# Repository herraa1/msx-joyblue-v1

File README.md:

# Bluetooth controller adapter for MSX (msx-joyblue) v1

Connect Bluetooth controllers to [MSX computers](https://www.msx.org/wiki/)

> [!NOTE]
>
> An adapter based on PCB v1 Build1a has been successfully built and tested using the bluepad32 firmware!
>
> Adapter v1 Build2b has NOT yet been built, although I may build it in the future.
>
> The other builds will NOT be built, and are just left for reference.
>

For an upgraded SMD version, please visit [msx-joyblue-v2](https://github.com/herraa1/msx-joyblue-v2).

## Introduction

The msx-joyblue is an adapter that allows connecting Bluetooth controllers to [MSX general purpose ports](https://www.msx.org/wiki/General_Purpose_port).

The adapter is based on the [unijoysticle2](https://github.com/ricardoquesada/unijoysticle2) and [bluepad32](https://github.com/ricardoquesada/bluepad32) projects, both owned by Ricardo Quesada.

The main features of the msx-joyblue v1 adapter are:
* small size
* made of widely available electronic components
* uses easy to solder through-hole components to lower the skills needed to build the adapter
* emulates up to two MSX joysticks
* attaches to MSX computers using female standard DE9 connectors
* formally requires an external USB power supply as the adapter draws slightly more current than two MSX ports can officially provide
* optionally, can be powered using MSX general purpose ports without an external power supply if your MSX can safely supply enough current
* builtin leds provide information about the operation of the adapter

## [Hardware](hardware/kicad/)

The msx-joyblue v1 adapter uses an ESP32-WROOM-32E based development board (either a [ESP32-DevKitC-32E](https://www.espressif.com/en/products/devkits/esp32-devkitc) board or a [NodeMCU-32 V1.3](docs/NodeMCU32-S_specification_V1.3.pdf) board) to convert the Bluetooth controller actions to the [MSX joystick standard signalling](https://www.msx.org/wiki/Joystick_control).

A printed circuit board (PCB) is used to easily bind all components:
* The ESP32 adapter board is connected using female headers
* PH2.0 connectors are used to connect cable extensions
* A 2.54 pitch I2C header is added for future extensions
* Jumpers are provided to enable different power options
* Only through-hole components are used

Connection to the MSX general purpose ports is implemented using a DE9 joystick extension cables with a female DE9 connector on one side and a loose end on the other side.
The MSX joystick extension cable loose end is wired according to the following pinout mapping.

|  |
|:--|
| MSX joystick connector pinout, from controller plug side |

| MSX side pin | Cable color (may vary) | Signal |
| ------------ | ---------------------- | ------ |
| 5            | Brown                  | +5v    |
| 4            | Orange                 | RIGHT  |
| 3            | Grey                   | LEFT   |
| 2            | Black                  | DOWN   |
| 1            | Red                    | UP     |
| 6            | Green                  | TRIG1  |
| 7            | White                  | TRIG2  |
| 8            | Blue                   | STROBE |
| 9            | Yellow                 | GND    |

### Build1a

[Bill Of Materials (BoM)](https://htmlpreview.github.io/?https://raw.githubusercontent.com/herraa1/msx-joyblue-v1/main/hardware/kicad/msx-joyblue-v1/bom/ibom.html)

The Build1a adapter ignores the MSX general purpose pin8 (OUT) signal. This is not a problem in general, but can cause incompatibilities with specific software, like MSX-HID [^2], which uses pin8 to try to guess which kind of device is connected to a MSX general purpose port. For MSX-HID, holding the Trigger B button, will put the software in FM-Towns compatible mode which will make the adapter functional.

This build uses open collector outputs (via [74LS05 hex inverters with open collector outputs](https://www.ti.com/lit/ds/symlink/sn7405.pdf)) which makes the adapter safer [^3] than the standard MSX joystick schematic depicted in the MSX Technical Data Book, as it avoids a series of undesired conditions that can lead to bus contention/short circuits.

||
|:--|
|msx-joyblue-v1 Build1a without case|

### Build2 (deprecated)

> [!WARNING]
> Build2 will not be finally built! Use at your own risk!
>
> Build2 has been superseded by Build2b.

The Build2 adapter takes into account the MSX general purpose pin8 (OUT) signal:
* When pin8 is HIGH, the adapter puts all stick and triggers signals in high impedance mode irrespective of their status (as if stick and triggers were not hold in the standard MSX joystick schematic), which become HIGH on the MSX side via the MSX PSG related circuitry pull-ups (matching the expected behavior)
* When pin8 is LOW
  * if a stick direction or trigger is hold, the corresponding signal is pulled down to GND causing it to be LOW (matching the expected behavior)
  * if a stick direction or trigger is not hold, the corresponding signal is put in high impedance mode, which becomes HIGH on the MSX side via the MSX PSG related circuitry pull-ups (matching the expected behavior)
  
This build uses discrete logic components to honor the pin8 signaling (a [74LS04 hex inverter](https://www.ti.com/lit/ds/symlink/sn74ls04.pdf) and three [74LS03 quad 2-input positive-nand gates with open collector outputs](https://www.ti.com/lit/ds/symlink/sn74ls03.pdf)) and uses open collector outputs which makes the adapter safer [^3] than the standard MSX joystick schematic depicted in the MSX Technical Data Book, as it avoids a series of undesired conditions that can lead to bus contention/short circuits.

||
|:--|
|msx-joyblue-v1 Build2 render|

### Build2b

> [!WARNING]
> Build2b has NOT yet been tested! Use at your own risk!

The Build2b is similar to Build2 but simplifies the BOM by using less different components.
 
This build uses discrete logic components to honor the pin8 signaling (four [74LS03 quad 2-input positive-nand gates with open collector outputs](https://www.ti.com/lit/ds/symlink/sn74ls03.pdf)) and uses open collector outputs which makes the adapter safer [^3] than the standard MSX joystick schematic depicted in the MSX Technical Data Book, as it avoids a series of undesired conditions that can lead to bus contention/short circuits.

||
|:--|
|msx-joyblue-v1 Build2b render|

### Build3

> [!WARNING]
> Build3 will not be finally built! Use at your own risk!

The Build3 adapter takes into account the MSX general purpose pin8 (OUT) signal, and produces outputs exactly as described for Build2.
  
This build uses GALs, instead of discrete logic components, to honor the pin8 signaling (two [ATF16V8B Electrically-Erasable Programmable Logic Device](https://ww1.microchip.com/downloads/en/devicedoc/atmel-0364-pld-atf16v8b-8bq-8bql-datasheet.pdf)) and uses open collector outputs which makes the adapter safer [^3] than the standard MSX joystick schematic depicted in the MSX Technical Data Book, as it avoids a series of undesired conditions that can lead to bus contention/short circuits.

||
|:--|
|msx-joyblue-v1 Build3 render|

## [Firmware](https://github.com/ricardoquesada/bluepad32/tree/develop)

The msx-joyblue v1 adapter firmware uses Ricardo Quesada [bluepad32](https://github.com/ricardoquesada/bluepad32/tree/main) library to drive Bluetooth controllers.
A [small modification](https://github.com/ricardoquesada/bluepad32/commit/9736bd169bc13ec625d469b8305d2ed2f46d6e69) to the library that enables support for MSX computers was commited to the _develop_ branch. The _main_ branch carries too the modification since February 2024.

See the [bluepad32 documentation](https://github.com/ricardoquesada/bluepad32/tree/main/docs) for [supported Bluetooth controllers](https://github.com/ricardoquesada/bluepad32/blob/main/docs/supported_gamepads.md).

## [Enclosure](enclosure/)

A simple acrylic enclosure is included.

||
|:--|
|msx-joyblue-v1 Build1a inside tested case prototype|

## Powering the msx-joyblue adapter

The msx-joyblue adapter uses about ~107mA when operating, while a single MSX general purpose port is capable of delivering up to 50mA according to the MSX standard [^1].
That means that even using two MSX general purpose ports (50mA + 50mA = 100mA) we are slightly over (107mA) the max current specification for the MSX general purpose ports.

Thus, the safest way to power the msx-joyblue adapter is by powering it via the USB micro connector of the attached ESP32 board using an external 5V USB power supply. The board automatically powers up when using the USB micro connector without enabling any switch.

Nevertheless, even if the MSX especification puts such a low limit on the current that can be drawn from a general purpose port, real MSX hardware usually can safely deliver enough current for the msx-joyblue adapter to work correctly without harming our beloved classic computers.

Taking that into account, the msx-joyblue adapter has been enabled to be optionally powered by the MSX general purpose ports port A and port B.

To enable powering the msx-joyblue adapter from port A and/or port B, the switch J3 _JOY PWR_ must be first turned on by sliding the switch handle to the right.

> [!NOTE]
> A [1N5817 Schottky diode](https://www.onsemi.com/download/data-sheet/pdf/1n5817-d.pdf) D1 is used to avoid leaking current from the msx-joyblue adapter to the MSX in case the msx-joyblue adapter is powered by USB.
> And two Positive Temperature Coeficient (PTC) resettable fuses F3 and F4 of 50mA each protect the MSX general purpose ports port A and port B from excess of current in case something goes horribly wrong on the msx-joyblue adapter side, aligning to the MSX specification.

To power the msx-joyblue adapter using the MSX general purpose ports we must first understand how the PTC protections on the msx-joyblue adapter are implemented.

The selected PTCs are rated for 50mA which is the so called Hold Current (the maximum current that can flow in normal operation). There is also the Trip Current (the minimum current necessary for the PTC to move to high-resistance state) which for the selected PTCs is around 100mA. Those thresholds are dependent on temperature and voltage. And to make things more undeterministic, the behavior of the PTC when current is between those thresholds is undefined (it may trip or not).

In normal operation and for a room temperature of around 25 degrees Celsius, the selected PTCs in practice never trip below 75mA.

So **if our MSX computer can safely provide more than 50mA on each MSX general purpose port** (which is usually the case), we can connect both Port A and port B to the MSX computer and turn on the J3 _JOY PWR_ switch to power the msx-joyblue adapter. Note that we need to connect both ports even if we use just one Bluetooth gamepad, just to meet the power requirements.

From PCB board version 1a, two jumpers JP3 and JP4 can be used to bypass the PTC protections for port A and port B.

> [!WARNING]
> Bypassing the PTC protections may damage your MSX computer.
> Do not bypass the PTC protections unless you known what you are doing.

By closing JP3 (and/or JP4) and **if our MSX computer can safely provide more than 100mA on a single MSX general purpose port**, we can connect Port A (or Port B) to the MSX computer and turn on the J3 _JOY PWR_ switch to power the msx-joyblue adapter using a single joystick port.

In summary, we can use the following options to power the msx-joyblue adapter (from safest to less safe):
* via the ESP32 USB micro conector
  * leave open jumpers J3 and J4
  * turn off the J3 _JOY PWR_ switch
  * connect a 5V USB power supply to the ESP32 USB micro connector
* via two MSX general purpose ports, if your MSX can safely provide slightly more than 50mA on each MSX general purpose port
  * leave open jumpers J3 and J4
  * turn on the J3 _JOY PWR_ switch
  * connect both Port A and Port B to the MSX general purpose ports
* via one MSX general port, if your MSX can safely provide more than 100mA on each MSX general purpose port
  * close jumpers J3 and/or J4
  * turn on the J3 _JOY PWR_ switch
  * connect Port A or Port B to a MSX general purpose port

## Compatibility Tests

| **Model**                | **Adapter PCB v1 Build1a** |
|--------------------------|----------------------------|
| Sony MSX HB-101P         |          OK                |
| Sony MSX HB-501F         |          OK                |
| Toshiba MSX HX-10        |          OK                |
| Philips MSX2 VG-8235     |          OK                |
| Panasonic MSX2+ FS-A1WSX |          OK                |
| Omega MSX2+              |          OK                |
| MSXVR                    |          OK                |

## References

Ricardo Quesada bluepad32 library
* https://github.com/ricardoquesada/bluepad32

Ricardo Quesada Unijoysticle2 project
* https://github.com/ricardoquesada/unijoysticle2

MSX General Purpose port
* https://www.msx.org/wiki/General_Purpose_port

[^1]: https://www.msx.org/wiki/General_Purpose_port
[^2]: https://www.msx.org/wiki/MSX-HID
[^3]: https://www.msx.org/wiki/Joystick/joypad_controller (see "Undesired Conditions")

## Image Sources

* https://www.oshwa.org/open-source-hardware-logo/
* https://en.wikipedia.org/wiki/File:Numbered_DE9_Diagram.svg
* https://commons.wikimedia.org/wiki/File:Bluetooth.svg

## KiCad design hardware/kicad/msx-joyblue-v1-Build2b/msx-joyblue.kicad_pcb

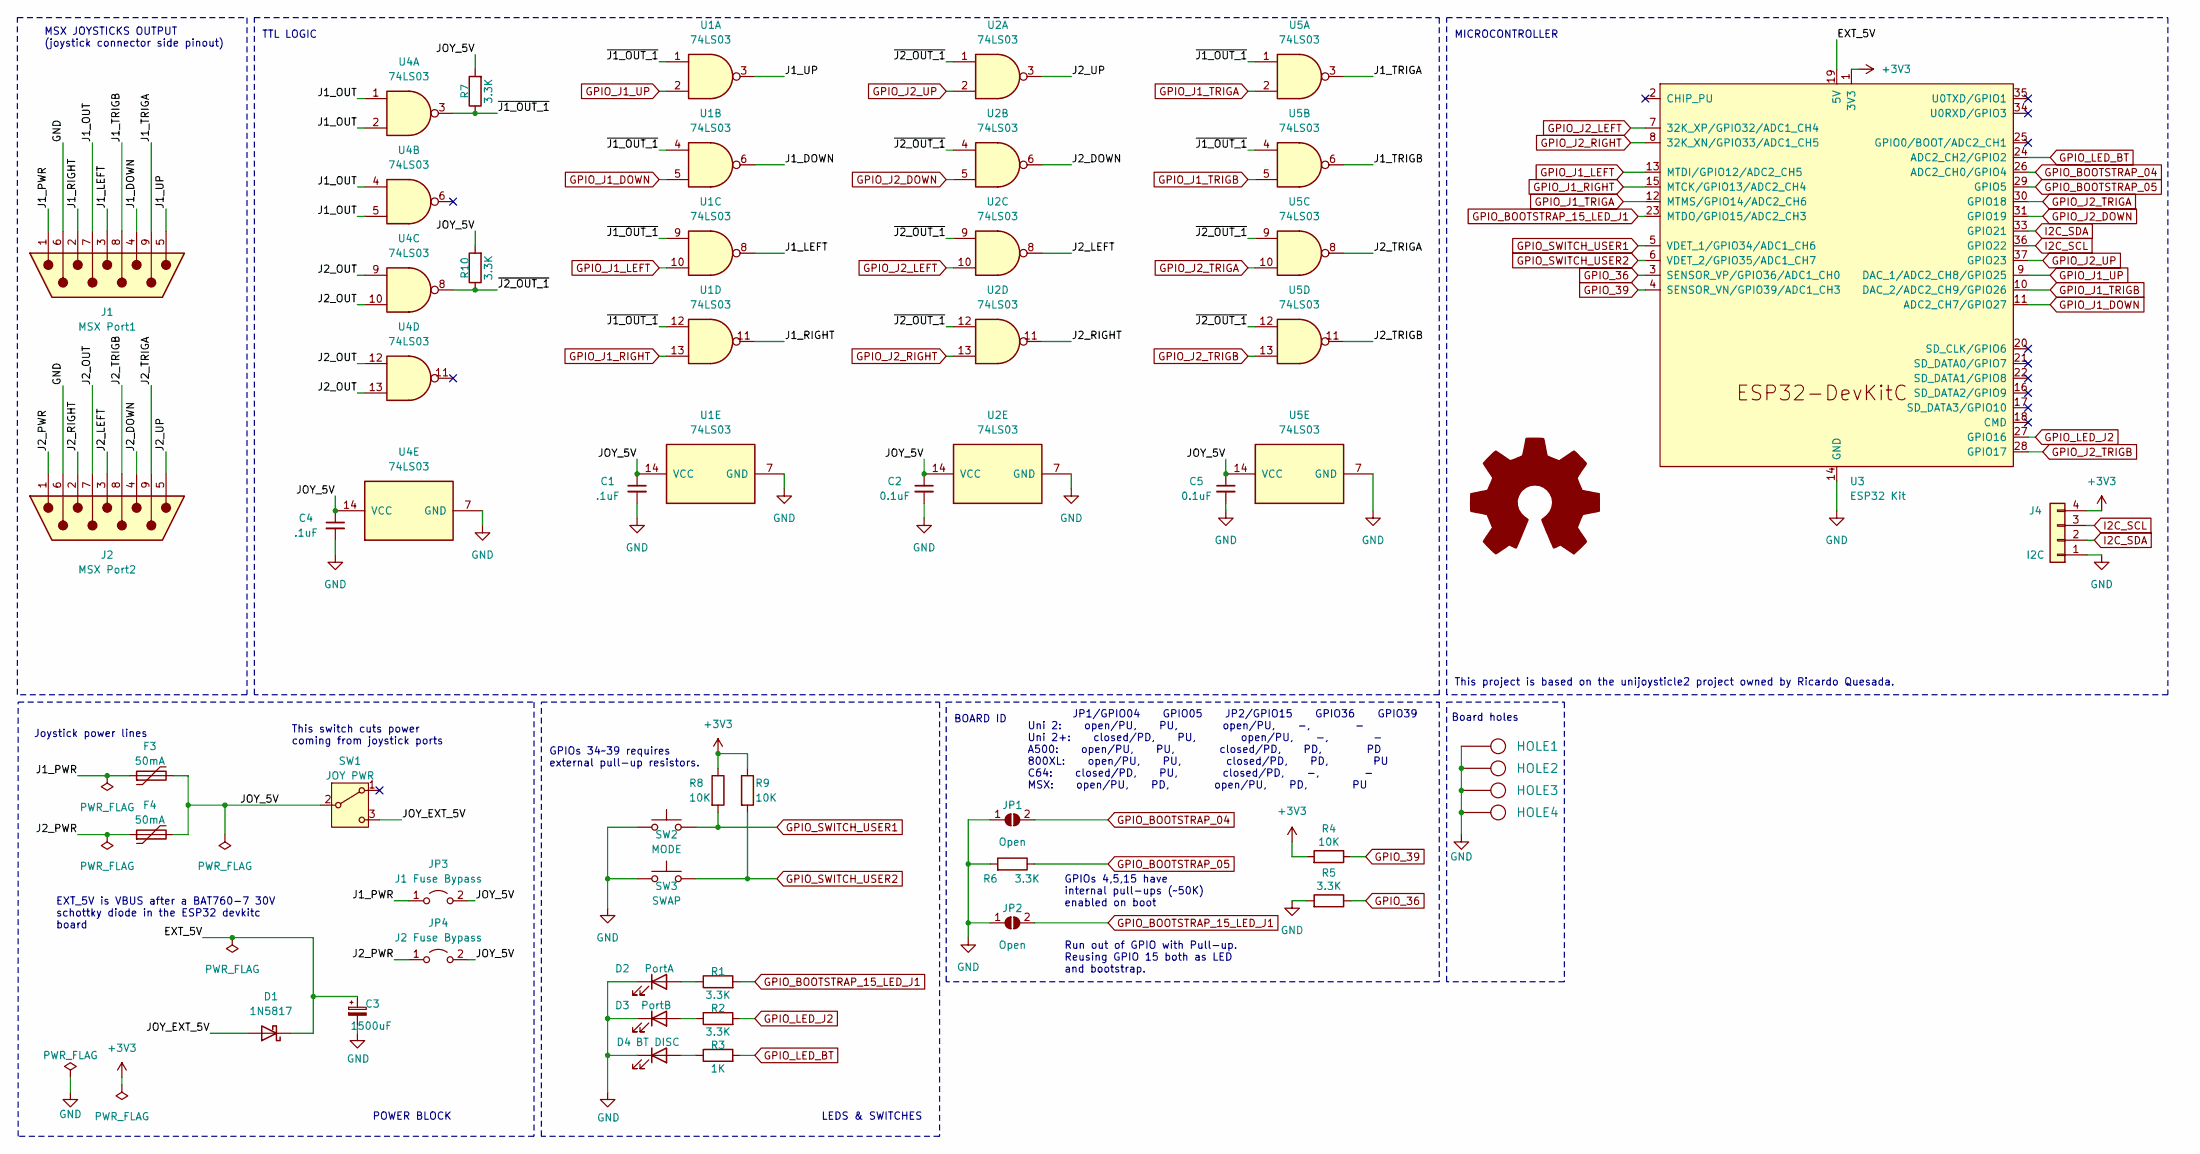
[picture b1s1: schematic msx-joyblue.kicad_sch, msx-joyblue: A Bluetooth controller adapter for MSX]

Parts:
C1, C4: .1uF; Cap_Cer_508
C2, C5: 0.1uF; Cap_Cer_508
C3: 1500uF; CP_Radial_D10.0mm_P5.00mm
D1: 1N5817; D_DO-41_SOD81_P10.16mm_Horizontal
D2: PortA; LED_D3.0mm
D3: PortB; LED_D3.0mm
D4: BT DISC; LED_D3.0mm
F3, F4: 50mA; C_Disc_D7.5mm_W2.5mm_P5.00mm
HOLE1, HOLE2, HOLE3, HOLE4: HOLE; Hole_3mm
J1: MSX Port1; JST_PH_B9B-PH-K_1x09_P2.00mm_Vertical
J2: MSX Port2; JST_PH_B9B-PH-K_1x09_P2.00mm_Vertical
J4: I2C; PinHeader_1x04_P2.54mm_Vertical
JP1, JP2: Open; SolderJumper-2_P1.3mm_Open_RoundedPad1.0x1.5mm
JP3: J1 Fuse Bypass; PinHeader_1x02_P2.54mm_Vertical
JP4: J2 Fuse Bypass; PinHeader_1x02_P2.54mm_Vertical
R1, R2, R7, R10: 3.3K; Res_762; LCSC C4310
R3: 1K; Res_762; LCSC C4310
R4, R8, R9: 10K; Res_762
R5, R6: 3.3K; Res_762
SW1: JOY PWR; SW_SK-12D07G6-1P2T-6mm
SW2: MODE; SW_Tactile_SPST_Angled_PTS645Vx39-2LFS
SW3: SWAP; SW_Tactile_SPST_Angled_PTS645Vx39-2LFS
SYM1: Logo_Open_Hardware_Large; OSHW-Logo_7.5x8mm_SilkScreen
U1, U2, U4, U5: 74LS03; DIP-14_W7.62mm_Socket_LongPads
U3: ESP32 Kit; X-NodeMCU-32-plus-ESP32-DevKitC

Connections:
+3V3: J4.4, R4.2, R8.1, R9.1, U3.1 (3V3)
/EXT_5V: C3.1, D1.1 (K), U3.19 (5V)
/J1_DOWN: J1.4, U1.6
/J1_LEFT: J1.3, U1.8
/J1_OUT: J1.7, U4.1, U4.2, U4.4, U4.5
/J1_PWR: F3.1, J1.1, JP3.1 (A)
/J1_RIGHT: J1.2, U1.11
/J1_TRIGA: J1.9, U5.3
/J1_TRIGB: J1.8, U5.6
/J1_UP: J1.5, U1.3
/J2_DOWN: J2.4, U2.6
/J2_LEFT: J2.3, U2.8
/J2_OUT: J2.7, U4.9, U4.10, U4.12, U4.13
/J2_PWR: F4.1, J2.1, JP4.1 (A)
/J2_RIGHT: J2.2, U2.11
/J2_TRIGA: J2.9, U5.8
/J2_TRIGB: J2.8, U5.11
/J2_UP: J2.5, U2.3
/JOY_5V: C1.1, C2.1, C4.1, C5.1, F3.2, F4.2, JP3.2 (B), JP4.2 (B), R7.2, R10.2, SW1.2 (B), U1.14 (VCC), U2.14 (VCC), U4.14 (VCC), U5.14 (VCC)
/JOY_EXT_5V: D1.2 (A), SW1.3 (C)
/~J1_OUT_1: R7.1, U1.1, U1.4, U1.9, U1.12, U4.3, U5.1, U5.4
/~J2_OUT_1: R10.1, U2.1, U2.4, U2.9, U2.12, U4.8, U5.9, U5.12
GND: C1.2, C2.2, C3.2, C4.2, C5.2, D2.1 (K), D3.1 (K), D4.1 (K), HOLE1.1, HOLE2.1, HOLE3.1, HOLE4.1, J1.6, J2.6, J4.1, JP1.1 (A), JP2.1 (A), R5.2, R6.2, SW2.1, SW3.1, U1.7 (GND), U2.7 (GND), U3.14 (GND), U3.32 (GND), U3.38 (GND), U4.7 (GND), U5.7 (GND)
GPIO_36: R5.1, U3.3 (SENSOR_VP/GPIO36/ADC1_CH0)
GPIO_39: R4.1, U3.4 (SENSOR_VN/GPIO39/ADC1_CH3)
GPIO_BOOTSTRAP_04: JP1.2 (B), U3.26 (ADC2_CH0/GPIO4)
GPIO_BOOTSTRAP_05: R6.1, U3.29 (GPIO5)
GPIO_BOOTSTRAP_15_LED_J1: JP2.2 (B), R1.2, U3.23 (MTDO/GPIO15/ADC2_CH3)
GPIO_J1_DOWN: U1.5, U3.11 (ADC2_CH7/GPIO27)
GPIO_J1_LEFT: U1.10, U3.13 (MTDI/GPIO12/ADC2_CH5)
GPIO_J1_RIGHT: U1.13, U3.15 (MTCK/GPIO13/ADC2_CH4)
GPIO_J1_TRIGA: U3.12 (MTMS/GPIO14/ADC2_CH6), U5.2
GPIO_J1_TRIGB: U3.10 (DAC_2/ADC2_CH9/GPIO26), U5.5
GPIO_J1_UP: U1.2, U3.9 (DAC_1/ADC2_CH8/GPIO25)
GPIO_J2_DOWN: U2.5, U3.31 (GPIO19)
GPIO_J2_LEFT: U2.10, U3.7 (32K_XP/GPIO32/ADC1_CH4)
GPIO_J2_RIGHT: U2.13, U3.8 (32K_XN/GPIO33/ADC1_CH5)
GPIO_J2_TRIGA: U3.30 (GPIO18), U5.10
GPIO_J2_TRIGB: U3.28 (GPIO17), U5.13
GPIO_J2_UP: U2.2, U3.37 (GPIO23)
GPIO_LED_BT: R3.2, U3.24 (ADC2_CH2/GPIO2)
GPIO_LED_J2: R2.2, U3.27 (GPIO16)
GPIO_SWITCH_USER1: R8.2, SW2.2, U3.5 (VDET_1/GPIO34/ADC1_CH6)
GPIO_SWITCH_USER2: R9.2, SW3.2, U3.6 (VDET_2/GPIO35/ADC1_CH7)
I2C_SCL: J4.3, U3.36 (GPIO22)
I2C_SDA: J4.2, U3.33 (GPIO21)
unnamed: D2.2 (A), R1.1
unnamed: D3.2 (A), R2.1
unnamed: D4.2 (A), R3.1

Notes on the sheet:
LEDS & SWITCHES
JP1/GPIO04 GPIO05 JP2/GPIO15 GPIO36 GPIO39 Uni 2: open/PU, PU, open/PU, -, - Uni 2+: closed/PD, PU, open/PU, -, - A500: open/PU, PU, closed/PD, PD, PD 800XL: open/PU, PU, closed/PD, PD, PU C64: closed/PD, PU, closed/PD, -, - MSX: open/PU, PD, open/PU, PD, PU
MSX JOYSTICKS OUTPUT (joystick connector side pinout)
POWER BLOCK
Joystick power lines
This switch cuts power coming from joystick ports
GPIOs 34~39 requires external pull-up resistors.
Run out of GPIO with Pull-up. Reusing GPIO 15 both as LED and bootstrap.
TTL LOGIC
GPIOs 4,5,15 have internal pull-ups (~50K) enabled on boot
Board holes
MICROCONTROLLER
EXT_5V is VBUS after a BAT760-7 30V schottky diode in the ESP32 devkitc board
This project is based on the unijoysticle2 project owned by Ricardo Quesada.
BOARD ID

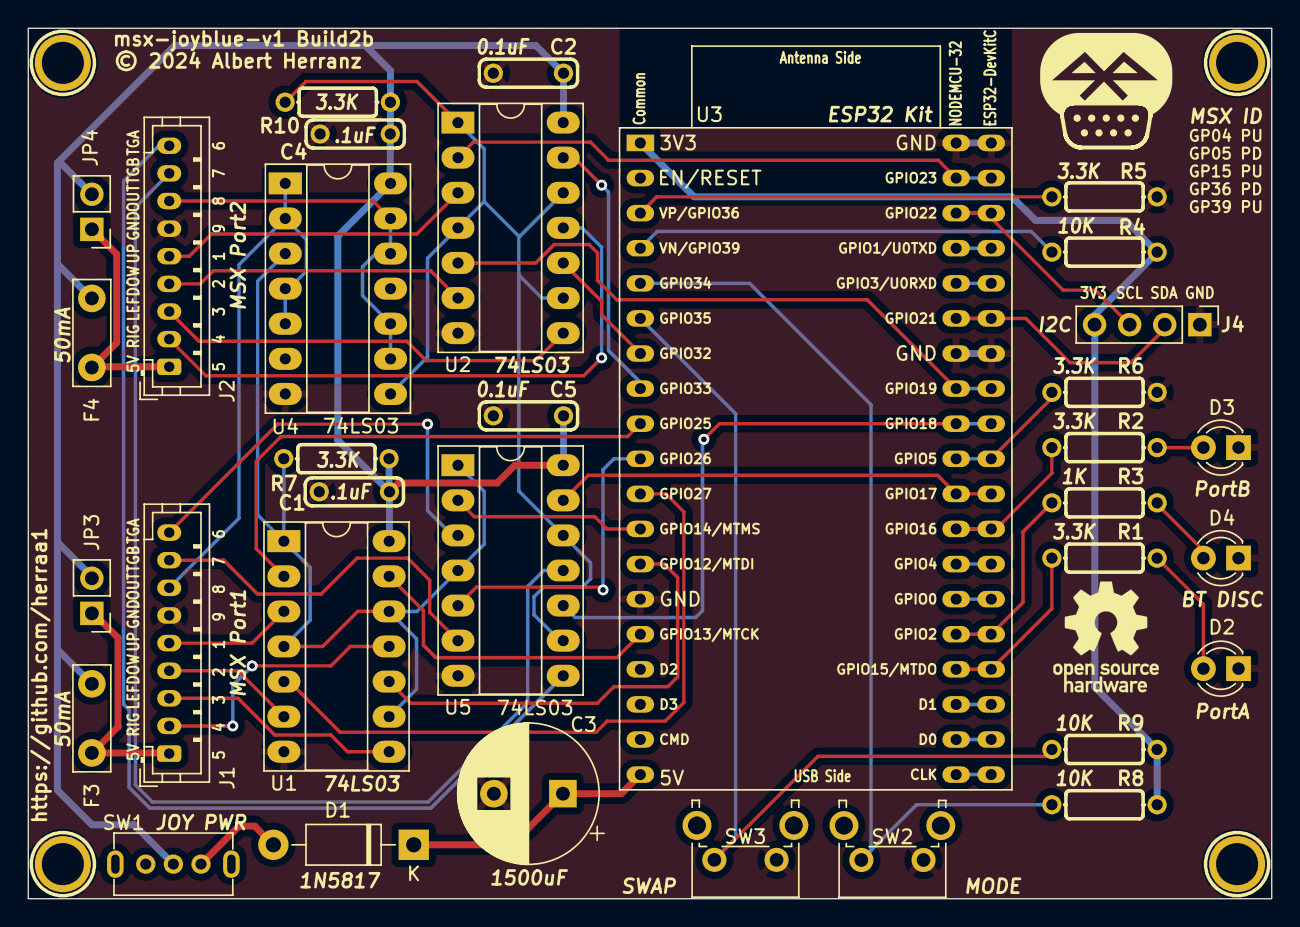
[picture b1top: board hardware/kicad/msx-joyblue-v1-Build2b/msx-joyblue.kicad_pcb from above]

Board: 2 copper layers, 90.0 x 63.0 mm, 39 parts (0 on the bottom side), 48 nets.

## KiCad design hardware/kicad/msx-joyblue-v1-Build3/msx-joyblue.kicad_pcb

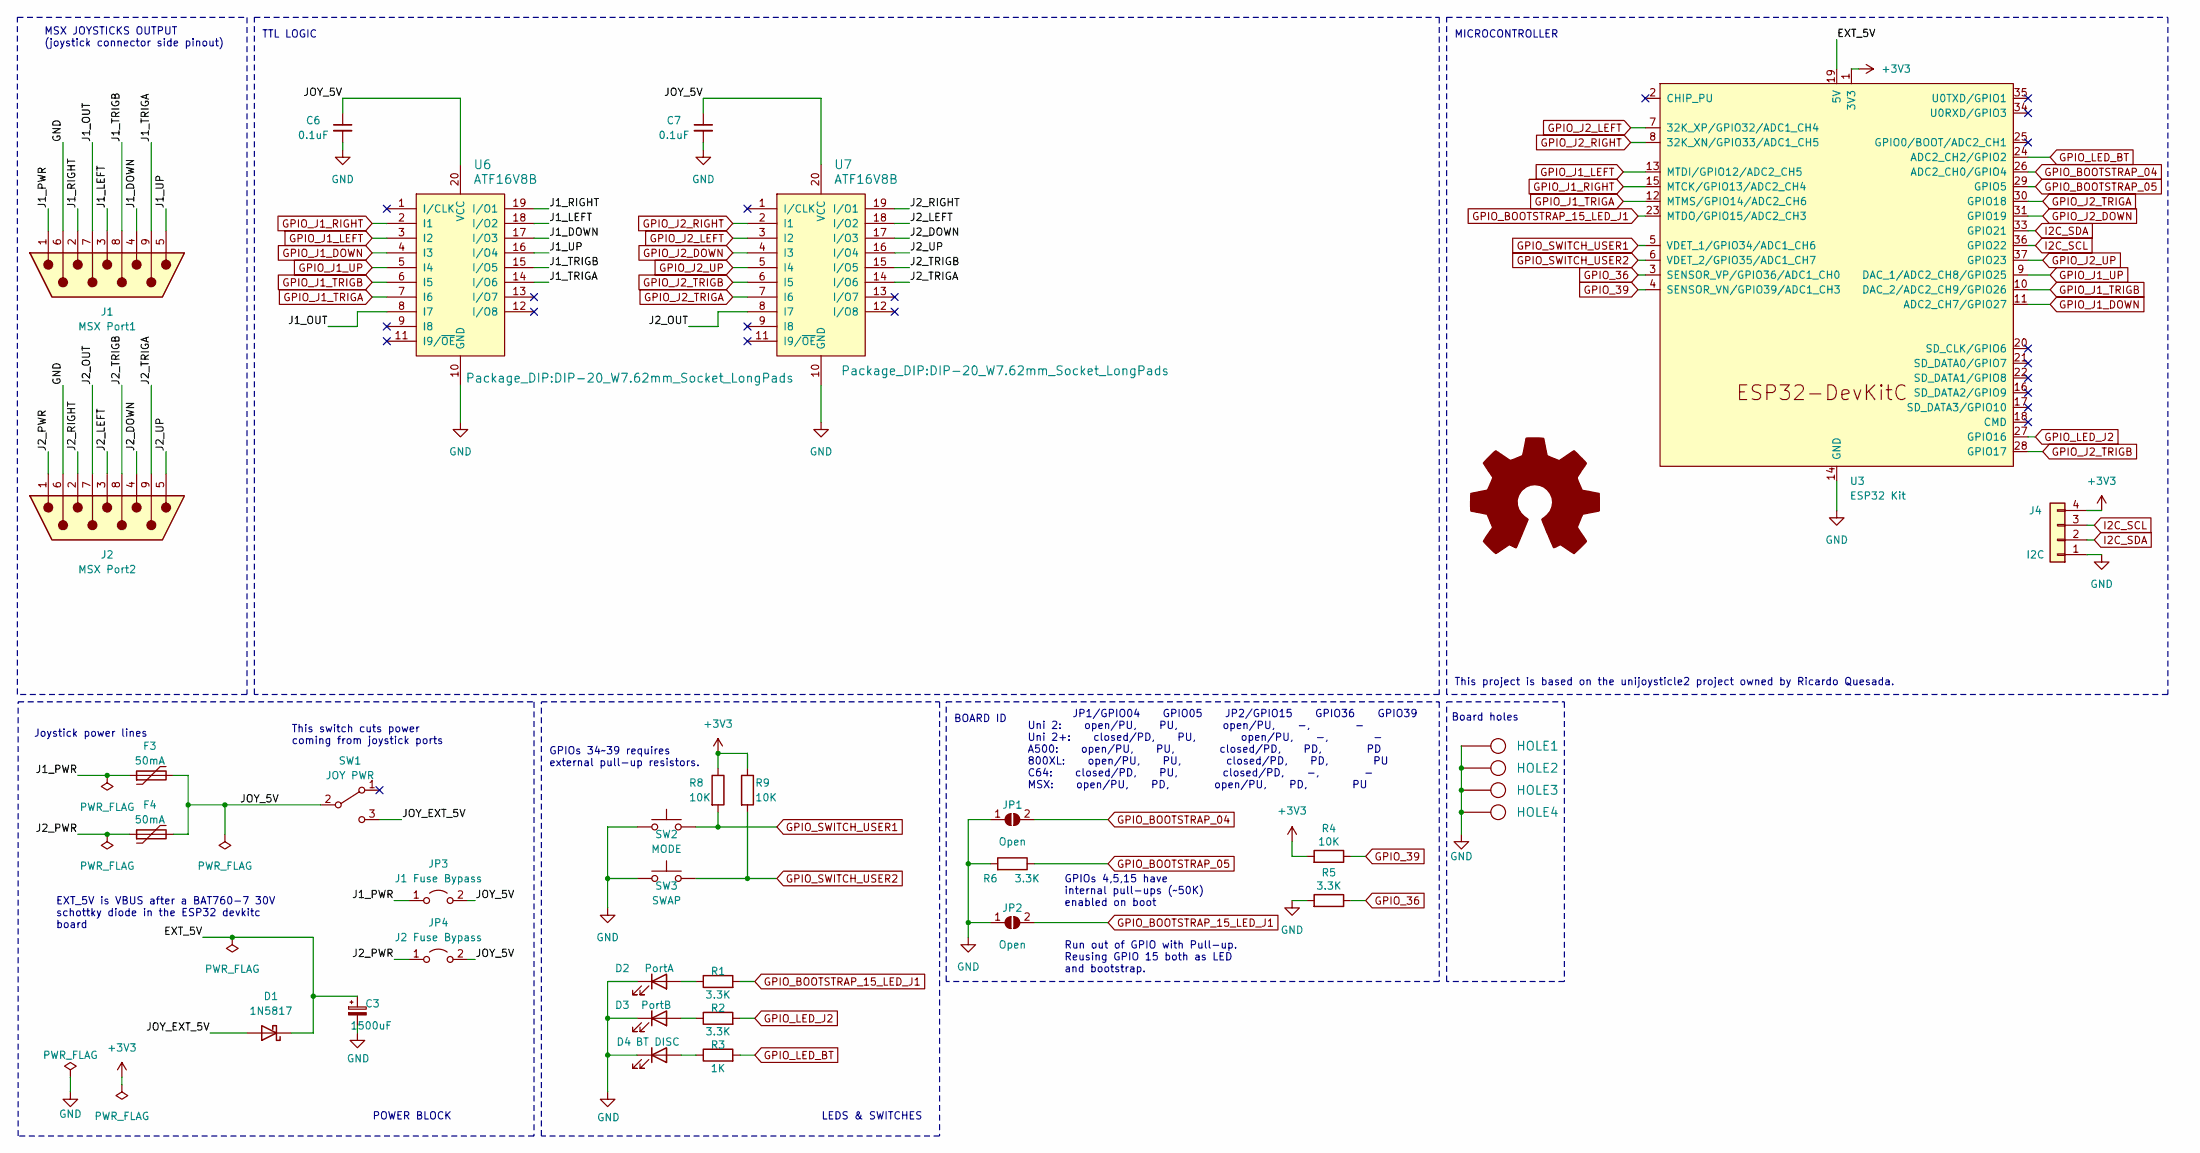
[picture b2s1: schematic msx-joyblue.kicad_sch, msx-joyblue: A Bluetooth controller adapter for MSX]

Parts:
C3: 1500uF; CP_Radial_D10.0mm_P5.00mm
C6, C7: 0.1uF; Cap_Cer_508
D1: 1N5817; D_DO-41_SOD81_P10.16mm_Horizontal
D2: PortA; LED_D3.0mm
D3: PortB; LED_D3.0mm
D4: BT DISC; LED_D3.0mm
F3, F4: 50mA; C_Disc_D7.5mm_W2.5mm_P5.00mm
HOLE1, HOLE2, HOLE3, HOLE4: HOLE; Hole_3mm
J1: MSX Port1; JST_PH_B9B-PH-K_1x09_P2.00mm_Vertical
J2: MSX Port2; JST_PH_B9B-PH-K_1x09_P2.00mm_Vertical
J4: I2C; PinHeader_1x04_P2.54mm_Vertical
JP1, JP2: Open; SolderJumper-2_P1.3mm_Open_RoundedPad1.0x1.5mm
JP3: J1 Fuse Bypass; PinHeader_1x02_P2.54mm_Vertical
JP4: J2 Fuse Bypass; PinHeader_1x02_P2.54mm_Vertical
R1, R2: 3.3K; Res_762; LCSC C4310
R3: 1K; Res_762; LCSC C4310
R4, R8, R9: 10K; Res_762
R5, R6: 3.3K; Res_762
SW1: JOY PWR; SW_SK-12D07G6-1P2T-6mm
SW2: MODE; SW_Tactile_SPST_Angled_PTS645Vx39-2LFS
SW3: SWAP; SW_Tactile_SPST_Angled_PTS645Vx39-2LFS
SYM1: Logo_Open_Hardware_Large; OSHW-Logo_7.5x8mm_SilkScreen
U3: ESP32 Kit; X-NodeMCU-32-plus-ESP32-DevKitC
U6, U7: ATF16V8B; DIP-20_W7.62mm_Socket_LongPads

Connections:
+3V3: J4.4, R4.2, R8.1, R9.1, U3.1 (3V3)
/EXT_5V: C3.1, D1.1 (K), U3.19 (5V)
/J1_DOWN: J1.4, U6.17 (I/O3)
/J1_LEFT: J1.3, U6.18 (I/O2)
/J1_OUT: J1.7, U6.8 (I7)
/J1_PWR: F3.1, J1.1, JP3.1 (A)
/J1_RIGHT: J1.2, U6.19 (I/O1)
/J1_TRIGA: J1.9, U6.14 (I/O6)
/J1_TRIGB: J1.8, U6.15 (I/O5)
/J1_UP: J1.5, U6.16 (I/O4)
/J2_DOWN: J2.4, U7.17 (I/O3)
/J2_LEFT: J2.3, U7.18 (I/O2)
/J2_OUT: J2.7, U7.8 (I7)
/J2_PWR: F4.1, J2.1, JP4.1 (A)
/J2_RIGHT: J2.2, U7.19 (I/O1)
/J2_TRIGA: J2.9, U7.14 (I/O6)
/J2_TRIGB: J2.8, U7.15 (I/O5)
/J2_UP: J2.5, U7.16 (I/O4)
/JOY_5V: C6.1, C7.1, F3.2, F4.2, JP3.2 (B), JP4.2 (B), SW1.2 (B), U6.20 (VCC), U7.20 (VCC)
/JOY_EXT_5V: D1.2 (A), SW1.3 (C)
GND: C3.2, C6.2, C7.2, D2.1 (K), D3.1 (K), D4.1 (K), HOLE1.1, HOLE2.1, HOLE3.1, HOLE4.1, J1.6, J2.6, J4.1, JP1.1 (A), JP2.1 (A), R5.2, R6.2, SW2.1, SW3.1, U3.14 (GND), U3.32 (GND), U3.38 (GND), U6.10 (GND), U7.10 (GND)
GPIO_36: R5.1, U3.3 (SENSOR_VP/GPIO36/ADC1_CH0)
GPIO_39: R4.1, U3.4 (SENSOR_VN/GPIO39/ADC1_CH3)
GPIO_BOOTSTRAP_04: JP1.2 (B), U3.26 (ADC2_CH0/GPIO4)
GPIO_BOOTSTRAP_05: R6.1, U3.29 (GPIO5)
GPIO_BOOTSTRAP_15_LED_J1: JP2.2 (B), R1.2, U3.23 (MTDO/GPIO15/ADC2_CH3)
GPIO_J1_DOWN: U3.11 (ADC2_CH7/GPIO27), U6.4 (I3)
GPIO_J1_LEFT: U3.13 (MTDI/GPIO12/ADC2_CH5), U6.3 (I2)
GPIO_J1_RIGHT: U3.15 (MTCK/GPIO13/ADC2_CH4), U6.2 (I1)
GPIO_J1_TRIGA: U3.12 (MTMS/GPIO14/ADC2_CH6), U6.7 (I6)
GPIO_J1_TRIGB: U3.10 (DAC_2/ADC2_CH9/GPIO26), U6.6 (I5)
GPIO_J1_UP: U3.9 (DAC_1/ADC2_CH8/GPIO25), U6.5 (I4)
GPIO_J2_DOWN: U3.31 (GPIO19), U7.4 (I3)
GPIO_J2_LEFT: U3.7 (32K_XP/GPIO32/ADC1_CH4), U7.3 (I2)
GPIO_J2_RIGHT: U3.8 (32K_XN/GPIO33/ADC1_CH5), U7.2 (I1)
GPIO_J2_TRIGA: U3.30 (GPIO18), U7.7 (I6)
GPIO_J2_TRIGB: U3.28 (GPIO17), U7.6 (I5)
GPIO_J2_UP: U3.37 (GPIO23), U7.5 (I4)
GPIO_LED_BT: R3.2, U3.24 (ADC2_CH2/GPIO2)
GPIO_LED_J2: R2.2, U3.27 (GPIO16)
GPIO_SWITCH_USER1: R8.2, SW2.2, U3.5 (VDET_1/GPIO34/ADC1_CH6)
GPIO_SWITCH_USER2: R9.2, SW3.2, U3.6 (VDET_2/GPIO35/ADC1_CH7)
I2C_SCL: J4.3, U3.36 (GPIO22)
I2C_SDA: J4.2, U3.33 (GPIO21)
unnamed: D2.2 (A), R1.1
unnamed: D3.2 (A), R2.1
unnamed: D4.2 (A), R3.1

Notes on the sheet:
LEDS & SWITCHES
JP1/GPIO04 GPIO05 JP2/GPIO15 GPIO36 GPIO39 Uni 2: open/PU, PU, open/PU, -, - Uni 2+: closed/PD, PU, open/PU, -, - A500: open/PU, PU, closed/PD, PD, PD 800XL: open/PU, PU, closed/PD, PD, PU C64: closed/PD, PU, closed/PD, -, - MSX: open/PU, PD, open/PU, PD, PU
MSX JOYSTICKS OUTPUT (joystick connector side pinout)
POWER BLOCK
Joystick power lines
This switch cuts power coming from joystick ports
GPIOs 34~39 requires external pull-up resistors.
Run out of GPIO with Pull-up. Reusing GPIO 15 both as LED and bootstrap.
TTL LOGIC
GPIOs 4,5,15 have internal pull-ups (~50K) enabled on boot
Board holes
MICROCONTROLLER
EXT_5V is VBUS after a BAT760-7 30V schottky diode in the ESP32 devkitc board
This project is based on the unijoysticle2 project owned by Ricardo Quesada.
BOARD ID

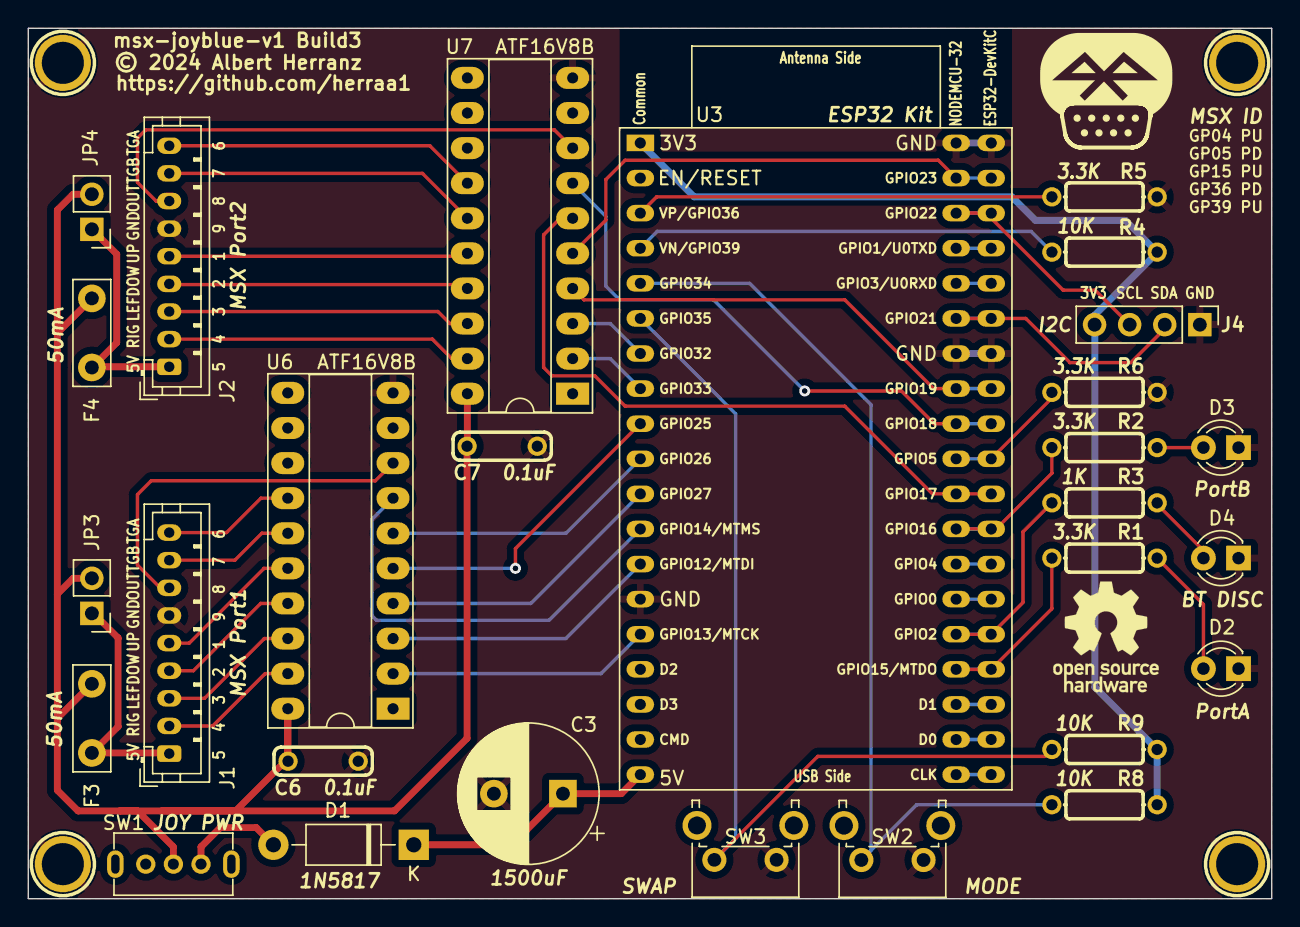
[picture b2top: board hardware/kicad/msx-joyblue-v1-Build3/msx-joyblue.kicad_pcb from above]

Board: 2 copper layers, 90.0 x 63.0 mm, 33 parts (0 on the bottom side), 46 nets.

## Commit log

2024-01-06 Added minimal project information
2024-01-06 Upload logo and DE9 images
2024-01-07 updated logo with new colors
2024-01-07 msx-joyblue support added to mainstream bluepad32 develop branch
2024-01-09 gitignore unpacked gerber files
2024-01-09 pcb: v1 build1
2024-01-10 pcb: v1 build1a
2024-01-10 add docs for nodemcu-32 board and ESP32-WROOM-32E package
2024-01-11 ordered first PCB build
2024-01-28 first PCB build tested, added untested enclosure
2024-01-28 added compatibility tests section
2024-01-29 added build1a picture
2024-02-01 readme: add initial acrylic case information
2024-02-11 build1: add information about pin8 behaviour
2024-02-11 enclosure: fix connector cutouts
2024-02-11 enclosure: update readme information
2024-02-11 hardware: add Build2 (untested)
2024-02-11 hardware: add Build3 (untested)
2024-02-11 readme: update warning
2024-02-11 readme: add renders for builds 2 and 3
2024-02-21 readme: behavior clarifications
2024-02-23 hardware: created v1 build2b board (untested)
2024-02-23 hardware: add missing pull-ups to v1 Build2b
2024-04-05 readme: update status
2024-04-06 readme: add interactive BoM for Build1a
2024-04-08 readme: link to msx-joyblue-v2
2024-04-27 readme: enclosure and minor status updates
2026-02-27 fix htmlpreview link

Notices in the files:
hardware/kicad/msx-joyblue-v1-Build2b/msx-joyblue.kicad_pcb:
© 2024 Albert Herranz
